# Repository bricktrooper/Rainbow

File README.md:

# Rainbow

Rainbow is an RGB controller board for LED strips.  It can be controlled over UART serial interface using the provided Python library.

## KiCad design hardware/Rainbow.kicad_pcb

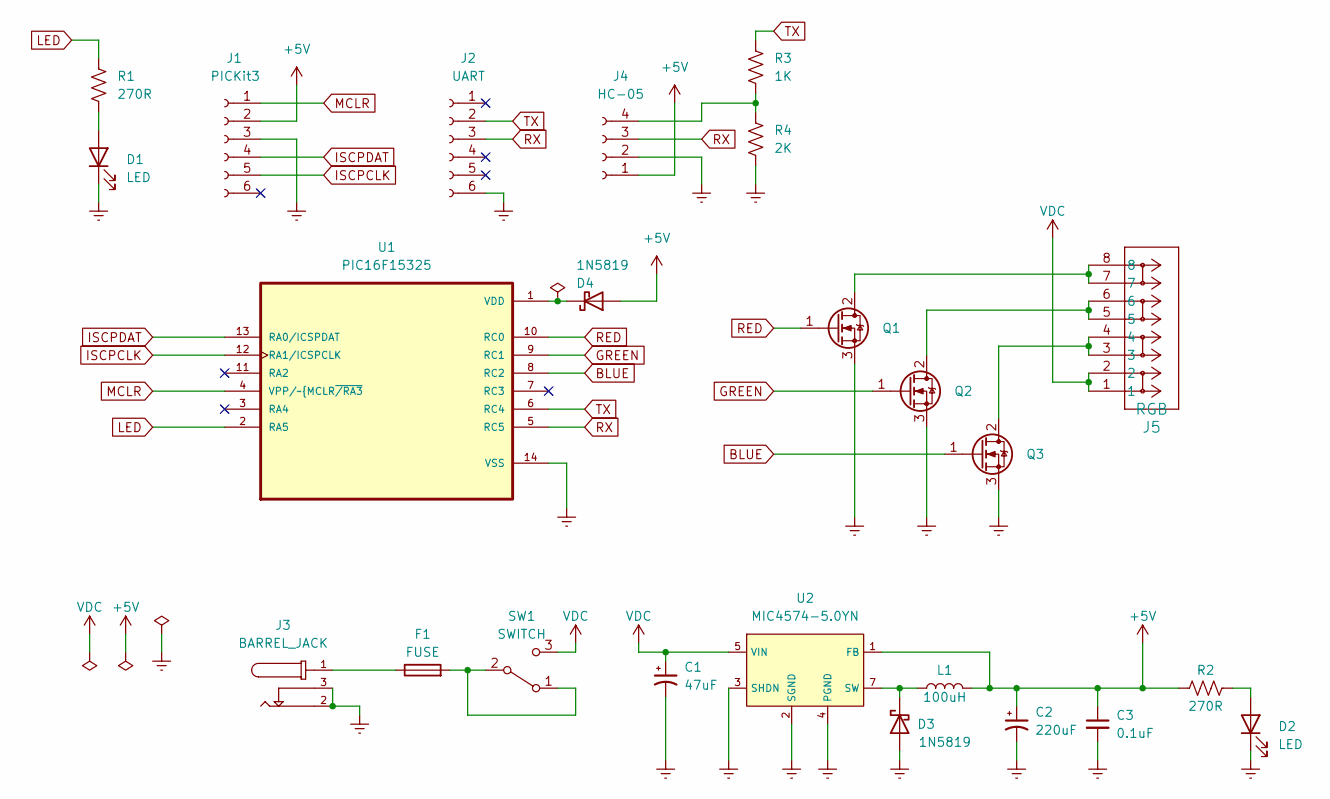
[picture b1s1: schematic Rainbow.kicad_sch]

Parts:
C1: 47uF; CP_Radial_D5.0mm_P2.50mm
C2: 220uF; CP_Radial_D6.3mm_P2.50mm
C3: 0.1uF; C_Disc_D3.0mm_W1.6mm_P2.50mm
D1, D2: LED; LED_D5.0mm
D3, D4: 1N5819; D_DO-41_SOD81_P7.62mm_Horizontal
F1: FUSE; Fuseholder_Blade_Mini_Keystone_3568
J1: PICKit3; PinSocket_1x06_P2.54mm_Vertical
J2: UART; PinSocket_1x06_P2.54mm_Vertical
J3: BARREL_JACK; Barrel_Jack; PARTREV A
J4: HC-05; PinSocket_1x04_P2.54mm_Vertical
J5: RGB; Wago
L1: 100uH; CP_Radial_Tantal_D4.5mm_P2.50mm
Q1, Q2, Q3: Q_NMOS_GDS; TO-220-3_Vertical
R1, R2: 270R; R_Axial_DIN0207_L6.3mm_D2.5mm_P7.62mm_Horizontal
R3: 1K; R_Axial_DIN0207_L6.3mm_D2.5mm_P7.62mm_Horizontal
R4: 2K; R_Axial_DIN0207_L6.3mm_D2.5mm_P7.62mm_Horizontal
SW1: SWITCH; CK_Switch
U1: PIC16F15325; DIP-14_W7.62mm_Socket_LongPads
U2: MIC4574-5.0YN; DIP-8_W7.62mm_Socket_LongPads

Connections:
+5V: C2.1, C3.1, D4.2 (A), J1.2, J4.1, L1.2, R2.1, U2.1 (FB)
BLUE: Q3.1 (G), U1.8 (RC2)
GNDREF: C1.2, C2.2, C3.2, D1.1 (K), D2.1 (K), D3.2 (A), J1.3, J2.6, J3.2, J3.3, J4.2, Q1.3 (S), Q2.3 (S), Q3.3 (S), R4.2, U1.14 (VSS), U2.2 (SGND), U2.3 (SHDN), U2.4 (PGND)
GREEN: Q2.1 (G), U1.9 (RC1)
ISCPCLK: J1.5, U1.12 (RA1/ICSPCLK)
ISCPDAT: J1.4, U1.13 (RA0/ICSPDAT)
LED: R1.1, U1.2 (RA5)
MCLR: J1.1, U1.4 (VPP/~MCLR~{/RA3)
unnamed: D1.2 (A), R1.2
unnamed: D2.2 (A), R2.2
unnamed: D3.1 (K), L1.1, U2.7 (SW)
unnamed: D4.1 (K), U1.1 (VDD)
unnamed: F1.1, J3.1
unnamed: F1.2, SW1.1 (A), SW1.2 (B)
unnamed: J4.4, R3.2, R4.1
unnamed: J5.3, J5.4, Q3.2 (D)
unnamed: J5.5, J5.6, Q2.2 (D)
unnamed: J5.7, J5.8, Q1.2 (D)
RED: Q1.1 (G), U1.10 (RC0)
RX: J2.3, J4.3, U1.5 (RC5)
TX: J2.2, R3.1, U1.6 (RC4)
VDC: C1.1, J5.1, J5.2, SW1.3 (C), U2.5 (VIN)

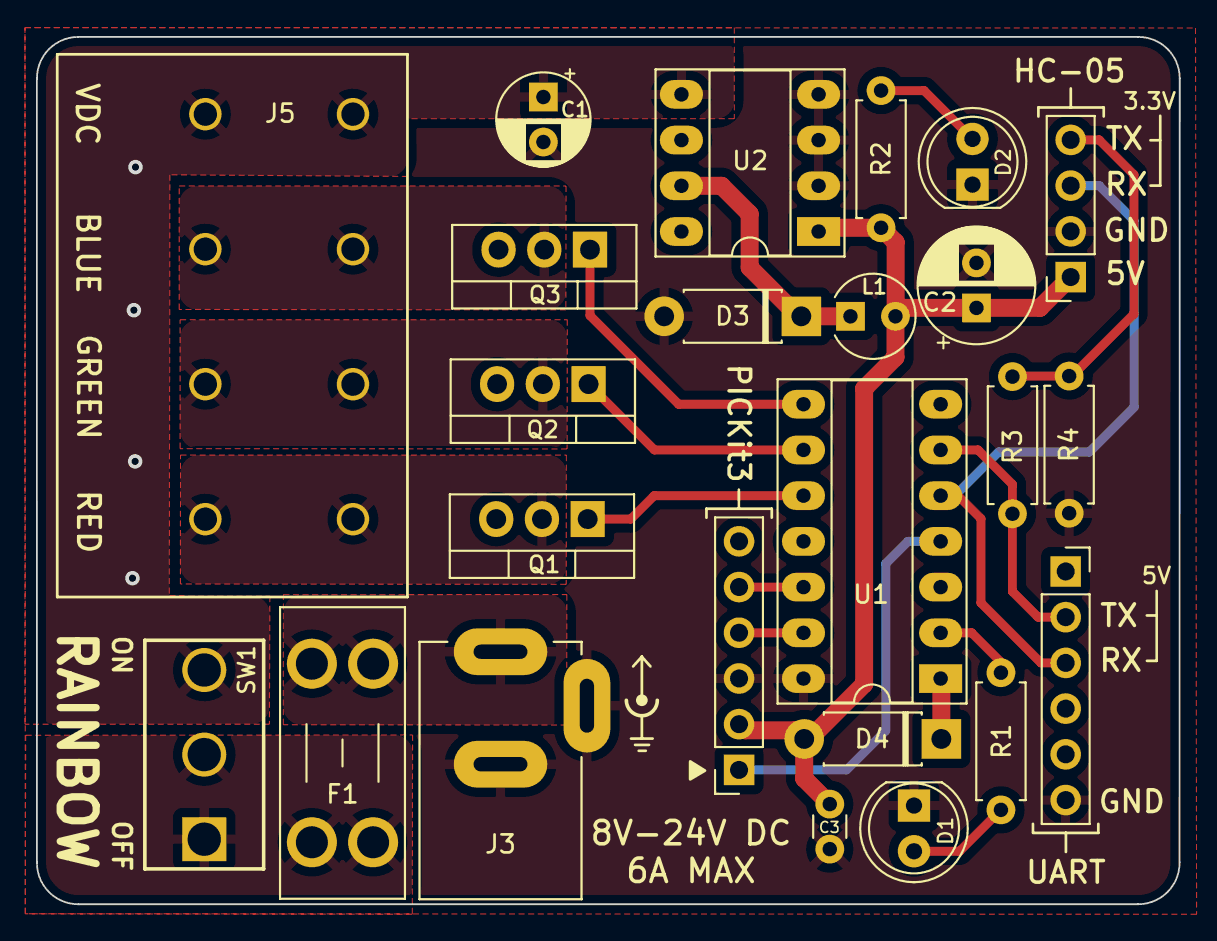
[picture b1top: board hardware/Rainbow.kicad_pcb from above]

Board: 2 copper layers, 63.5 x 48.2 mm, 24 parts (0 on the bottom side), 22 nets.

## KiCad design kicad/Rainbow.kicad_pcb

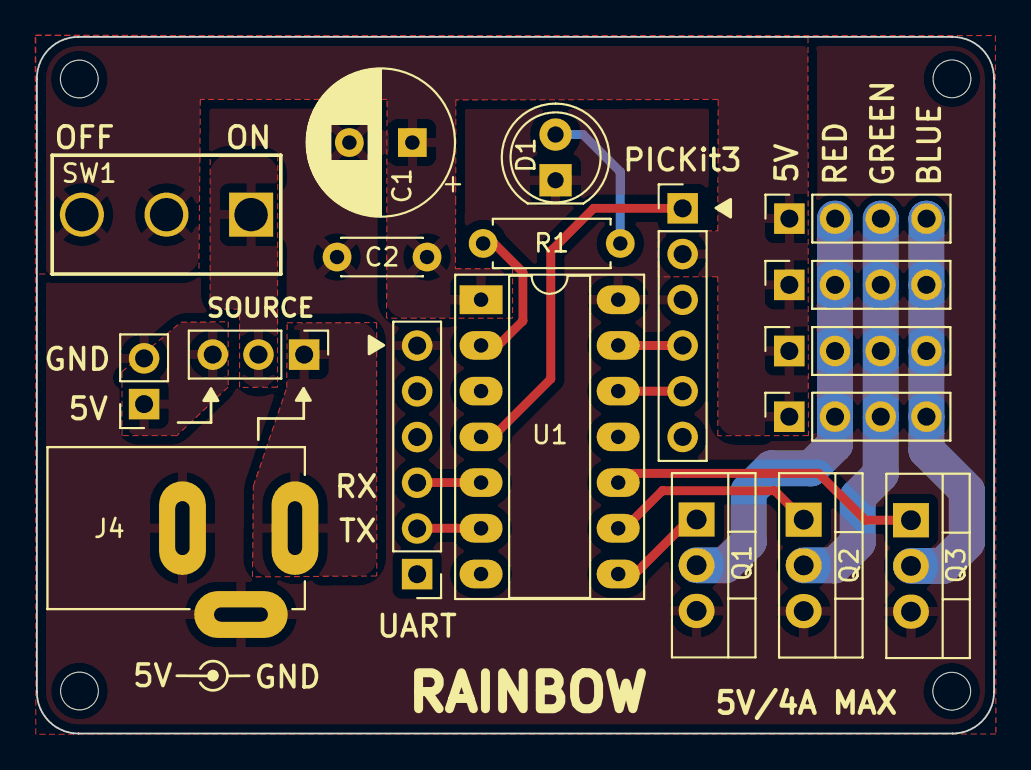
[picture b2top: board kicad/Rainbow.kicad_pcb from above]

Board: 2 copper layers, 53.2 x 38.7 mm, 22 parts (0 on the bottom side), 18 nets.

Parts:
C1: 470uF; CP_Radial_D8.0mm_P3.50mm
C2: 0.1uF; C_Disc_D4.3mm_W1.9mm_P5.00mm
D1: LED; LED_D5.0mm
H1, H2, H3, H4: MountingHole; MountingHole_2.1mm
J1: PICKit3; PinHeader_1x06_P2.54mm_Vertical
J2: UART; PinHeader_1x06_P2.54mm_Vertical
J3: JUMPER; PinSocket_1x02_P2.54mm_Vertical
J4: JACK; Tensility_Barrel_Jack
J5, J6, J7, J8: RGB; PinSocket_1x04_P2.54mm_Vertical
J9: SOURCE; PinHeader_1x03_P2.54mm_Vertical
Q1, Q2, Q3: Q_NMOS_GDS; TO-220-3_Vertical
R1: 270R; R_Axial_DIN0207_L6.3mm_D2.5mm_P7.62mm_Horizontal
SW1: SWITCH; CK_Switch
U1: PIC16F15325; DIP-14_W7.62mm_Socket_LongPads

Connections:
+5V: C1.1, C2.1, J1.2, J5.1, J6.1, J7.1, J8.1, SW1.2 (B), SW1.3 (C), U1.1 (VDD)
BLUE: Q3.1 (G), U1.10 (RC0)
GNDREF: C1.2, C2.2, D1.1 (K), J1.3, J2.6, J3.2, J4.2, J4.3, Q1.3 (S), Q2.3 (S), Q3.3 (S), U1.14 (VSS)
GREEN: Q2.1 (G), U1.9 (RC1)
ISCPCLK: J1.5, U1.12 (RA1/ICSPCLK)
ISCPDAT: J1.4, U1.13 (RA0/ICSPDAT)
LED: R1.1, U1.2 (RA5)
MCLR: J1.1, U1.4 (VPP/~MCLR~{/RA3)
unnamed: D1.2 (A), R1.2
unnamed: J3.1, J9.3
unnamed: J4.1, J9.1
unnamed: J5.2, J6.2, J7.2, J8.2, Q1.2 (D)
unnamed: J5.3, J6.3, J7.3, J8.3, Q2.2 (D)
unnamed: J5.4, J6.4, J7.4, J8.4, Q3.2 (D)
unnamed: J9.2, SW1.1 (A)
RED: Q1.1 (G), U1.8 (RC2)
RX: J2.3, U1.5 (RC5)
TX: J2.2, U1.6 (RC4)

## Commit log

2022-12-29 Generate KiCad project
2022-12-29 Preliminary schematic
2022-12-29 Schematic tweaks and untangle PCB ratsnest
2022-12-29 Add capacitors to power supply
2022-12-31 A bunch of stuff
2023-01-02 Finish PCB
2023-01-02 Finish up board
2023-01-04 tweak silk and placement
2023-01-05 Fix FET pins and traces
2023-01-30 Folder renaming
2023-01-30 gitignores
2023-01-30 Ignore build artifacts
2023-01-30 Datasheets and user manuals
2023-01-30 Configuration words
2023-01-30 LED working
2023-01-31 initialization and 8 MHz clock
2023-02-06 WIP UART
2023-02-21 Fix clock switching
2023-02-21 UART1
2023-02-21 HC-05
2023-03-07 PWM working
2023-03-21 Add fuse
2023-03-21 echo
2023-03-21 Bottom 5V polygons
2023-03-22 Rename docs
2023-03-22 Rename artifacts folder
2023-03-22 Finish up PCB
2023-03-27 Notes for hardware rework
2023-03-29 Fix PWM duty cycle bugs
2023-03-29 PWM4 and PWM5
2023-03-29 RGB API with rainbow
2023-04-03 Protocol
2023-05-19 Re-engineer board for flexible power supply
2023-05-19 Finish wiring
2023-05-20 Clean up some PCB stuff
2023-05-20 0.1 uF bypass capacitor
2023-05-27 Change diode footprint
2023-05-27 Fix warnings and UART echo
2023-05-30 Diodes for reverse polarity protection
2023-05-30 Remove extra diode on RX line
2023-05-30 Datasheets
2023-05-31 Brightness parameter for rainbow
2023-05-31 Generate gerbers
2023-05-31 Firmware backbones
2023-07-08 Swap footprints for C1 and C2
2023-07-08 Blink LED slower on startup
2023-07-08 Cleanup
2023-07-08 PPS I/O enums
2023-07-08 Oscillator API
2023-07-08 Typedef PPS enums
2023-07-08 Interrupts API
2023-07-08 Abort and fatal routines
2023-07-08 Fatal UART on NULL pointer or overrun
2023-07-10 Abort reason
2023-07-10 Firmware service
2023-07-10 Python boilerplate
2023-07-10 Ping Rainbow from Python
2023-07-11 Typos
2023-07-12 Move PWM frequency beyond audible range
    The PWM frequency causes coil while in the power supply.
    Change the prescaler to increase the frequency beyond the
    audible range.
2023-07-13 timer2 API
2023-07-13 Colour enum lookup table for channels
2023-07-13 WIP software
2023-07-13 ramp functions
2023-07-13 Brightness control for each RGB channel
2023-07-13 Function naming
2023-07-13 Ramp scaling to account for brightness
2023-07-13 Simplify brightness implementation
2023-07-13 Combine all colours for brightness function
2023-07-13 naming
2023-07-13 Switch everything to 32 MHz
2023-07-13 comments
2023-07-14 Import queue implementation
2023-07-14 Blink timings
2023-07-14 Enable peripheral interrupts
2023-07-14 Async UART RX
2023-07-14 Async UART TX
2023-07-15 Make printf work with non-blocking mode
2023-07-15 Working ping
2023-07-15 Fix magic RX bug
2023-07-16 Clean up timer2
2023-07-16 Timer0 API
2023-07-16 Hide link RX state enum
2023-07-16 Rainbow update and cycle refactor
2023-07-17 Enable rainbow through opcode
2023-07-17 Renaming
2023-07-17 Link python API
2023-07-17 Rename main file
2023-07-18 Increase TX buffer for printing
2023-07-18 Ping working
2023-07-18 Timer2 interrupt enable function
2023-07-18 Add count parameter to led blink function
2023-07-18 Start with interrupts masked
2023-07-18 Timer2 clock source enums
2023-07-18 Remove timer0 interrupt for rainbow
    Interrupt starves UART interrupts so switch
    rainbow to poll for timer0 expiration instead.
    This adds overhead for updating the rainbow
    even when it is not active. Also repeated pings
    are not 100 % smooth but at least it seems to
    be stable (I hope).
2023-07-18 Clean up ping and rainbow commands
2023-07-18 Rainbow speed (not yet working)
2023-07-18 Add Logs submodule
2023-07-18 Add CLI submodule
2023-07-18 Connect imports to submodules
2023-07-18 Update log
2023-07-18 Rainbow command with adjustable speed
2023-07-18 UART debug and warning messages
2023-07-18 RGB colour command
2023-07-18 Encapsulate UART non-blocking and blocking modes
2023-07-18 Renaming of UART interrupt APIs
2023-07-18 Fancy colours for logs
2023-07-18 Fix CLI bug with brightness and colour
2023-07-18 Move RGB class to separate file
2023-07-18 Reboot command
2023-07-19 Update submodules
2023-07-19 Clean up firmware
2023-07-19 Relocate CLI functions
2023-07-19 CLI command to turn off lights
2023-07-19 Rename rainbow opcode to cycle
2023-07-19 Commas after last enum element
2023-07-19 Dictionary for subcommands
2023-07-19 Program prefix
2023-07-20 Remove submodules
2023-07-20 Create rainbow package
2023-07-20 Fix ping printing
2023-07-20 Refactoring and default command
2023-07-20 Fix cycle disable bug with timer flag
2023-07-20 setup.py for pip installation
2023-07-20 Wrapper function for turning lights off
2023-07-20 Test scripts
2023-07-20 Ping count
2023-07-20 Move tests
2023-07-20 Calculate ping latency
2023-07-20 Default settings in firmware
2023-07-25 Organize firmware files
2023-07-25 Move ISR to system module
2023-07-25 Get oscillator frequency
2023-07-25 Rename some functions
2023-07-25 Functions to change baud rate
2023-07-25 Firmware script to configure HC-05
2023-07-25 Remove UART purge functions
2023-07-25 Fix baud rate bug in HC-05 script
2023-07-25 Pass port to test scripts
2023-07-25 Default serial port
2023-07-25 Reorganize folders
2023-07-25 Installer script for rainbow command
2023-07-25 Installation instructions
2023-07-26 Simplify install script
2023-07-26 Fix installer errors
2023-07-26 Fix parameter range bugs
2023-07-26 Improve HC-05 reliability
2023-07-26 Make port optional in tests
2023-07-26 Reduce UART timeout
2023-07-26 Speed up HC-05 configuration
2023-07-26 Error checking for tests
2023-07-26 Purge on RX failure
2023-07-26 Rename default port functions
2024-07-22 Shebang fix and install PySerial
2025-01-14 Upload picture and demo video
